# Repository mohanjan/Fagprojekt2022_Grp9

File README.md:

CAPNA
=======================

## What is CAPNA?
CAPNA (Complementary Audio Processor Network Architecture), is a network configuration of individual CAPs (Complementary Audio Processor), each running different DSP applications. This network is synthesized from a con- figuration XML file, which allows the user to specify the interconnections between multible CAPs and the program each CAP runs. The intention with this architecture is to be an uncomplicated, scalable and application tailored digital signal processing.
CAPNA enables the user to accelerate algorithms within digital signal processing (DSP) such as FIR-filtering, machine learning (ML) such as Wavenet and arithmetic calculations such as summation or multiplication. For further explanation of our project please see the [poster](Poster-GRP09-COMPUTE22-1-DSP.pdf) and the [paper](PAPER_GRP09_COMPUTE22-1.pdf)

## Usage
CAPNA is setup using an [XML configuration file](Config) and programmed using [assembly files](Programs).
Once programmed and configured, chisel3 is then used to compile the CAPNA-network into a verilog file which is called DSP.V.

## Recomended development environment
To ease any development on or using CAPNA, [vowstar](https://github.com/vowstar) has made a dockerfile from which an working development debian enviroment can be created and used. we have added verilator to this file and included it here. his original repo can be found here: [https://github.com/vowstar/chisel3-docker](https://github.com/vowstar/chisel3-docker).
The environment contains the following tools:
- [git](https://git-scm.com/)
- [wget](https://www.gnu.org/software/wget/)
- bc(basic calculator)
- [rsync](https://linux.die.net/man/1/rsync)
- [gnupg gnu privacy guard](https://gnupg.org/)
- [curl](https://curl.se/)
- [zip/unzip](http://infozip.sourceforge.net/)
- [make](https://www.gnu.org/software/make/)
- [SBT](https://www.scala-sbt.org/)
- [Chisel3](https://github.com/chipsalliance/chisel3)
- [Verilator](https://www.veripool.org/verilator/)
- [Icaros verilog](http://iverilog.icarus.com/)
- [gtkwave](http://gtkwave.sourceforge.net/)
- [python3](https://www.python.org/)
- Vim
- build essentials(GNU debugger, g++/GNU compiler collection)
- default-jdk-headless
- tools for vivado

### Installation
Note: we recommend to install docker desktop and use the docker image to build a container to insure the function of CAPNA regardless of which system you are using.

To deploy a docker container using the image do the following:
Firstly build the image via the dockerfile calling it chisel3_dev using the command below
```cmd
docker build <path of folder containing dockerfile> -t chisel3_dev
```
To insure the build please check that it is there when the images are listed:

```cmd
docker image ls 
```

Then deploy a container called dev_container and run a bash terminal using the chisel3_dev image and mounting the capna folder location:

```cmd
docker run -it  --name dev_container -v <path\\CAPNA>:/<name of folder in the container> chisel3_dev
```

To manage the container use docker desktop.

To start another terminal using the runnning container dev_container use:
```cmd
docker exec -it dev_container bash
```

To install the tools mentioned above on a linux distribution or WSL(windows subsystem linux) copy paste the following into a bash terminal:
```bash
sudo apt-get update \
&& apt-get install -y \
git \
curl \
unzip \
zip \
verilator \
iverilog \
make \
gtkwave \
&& sudo curl -s "https://get.sdkman.io" | bash \
&& sdk install sbt \
&& sdk install java 11.0.15-tem \
```
### Uninstalling
To uninstall the tools used in the development environment cope paste the following into a bash terminal:
```bash
apt remove \
git \
curl \
unzip \
zip \
verilator \
iverilog \
make \
gtkwave \
rm -rf ~/.sdkman
```

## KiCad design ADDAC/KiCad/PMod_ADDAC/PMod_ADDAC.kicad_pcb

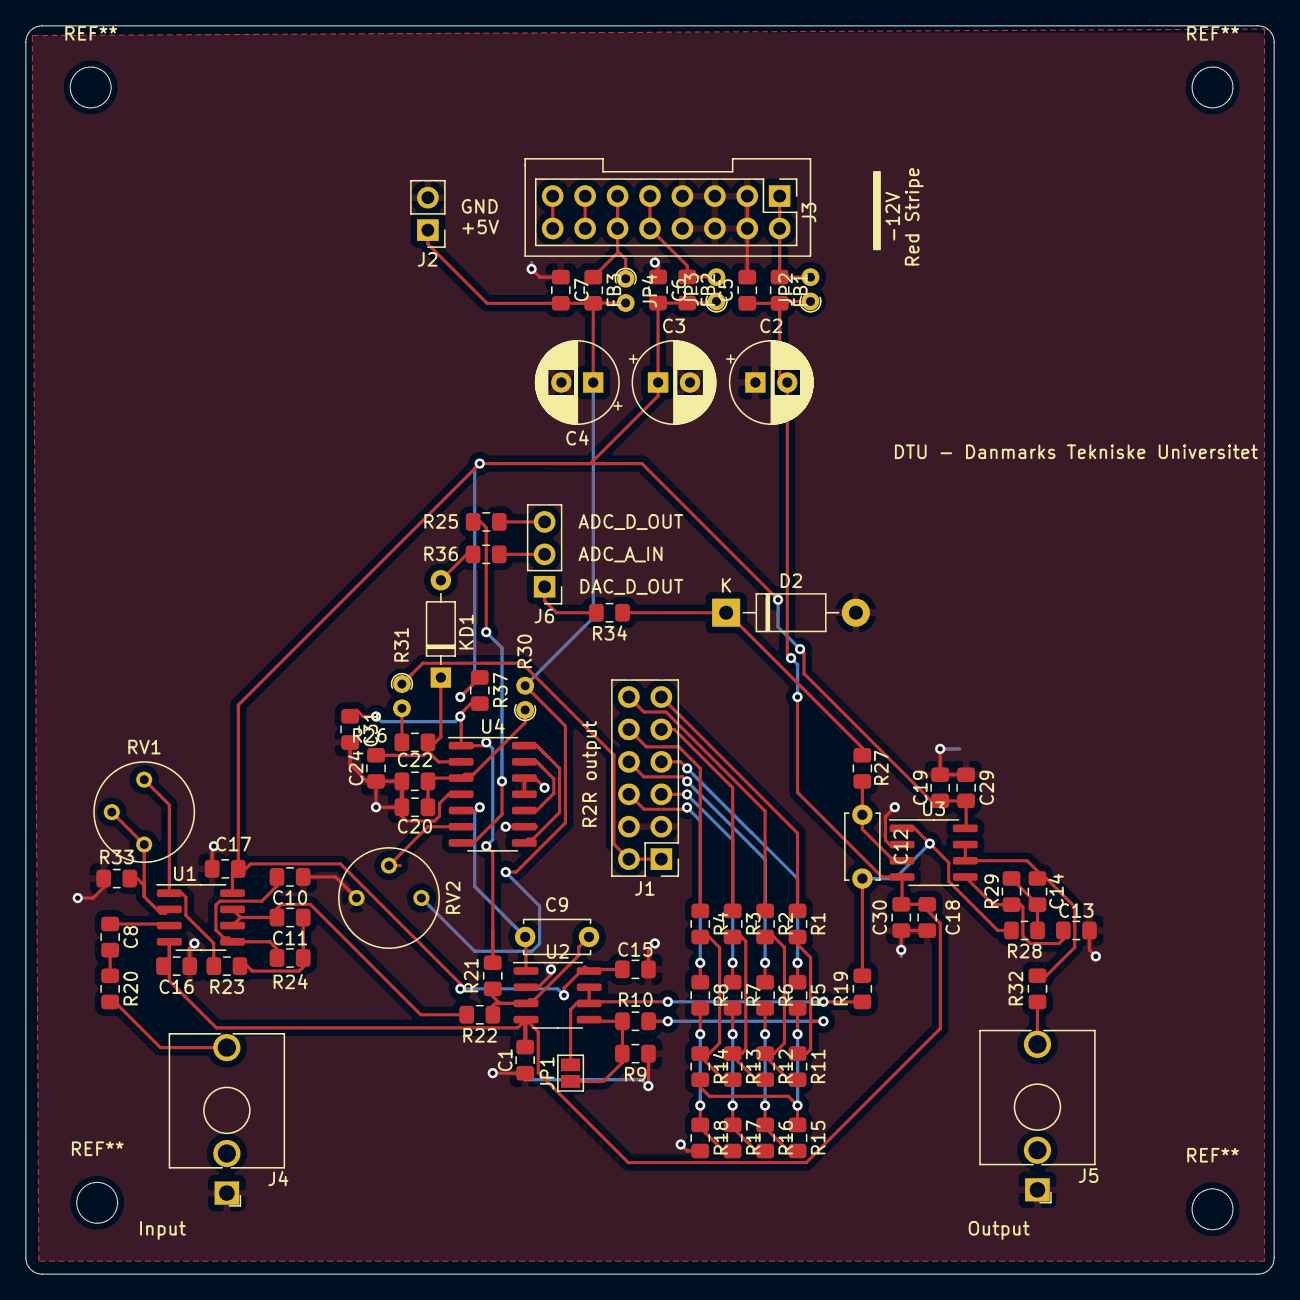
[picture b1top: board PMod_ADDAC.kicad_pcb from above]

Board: 2 copper layers, 97.8 x 97.8 mm, 82 parts (0 on the bottom side), 57 nets.

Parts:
C1, C15: 100; C_0805_2012Metric_Pad1.15x1.40mm_HandSolder
C2, C3, C4: 47u; CP_Radial_D6.3mm_P2.50mm
C5, C6, C7, C10, C11, C13, C14, C16, C17, C18, C19: 10n; C_0805_2012Metric_Pad1.15x1.40mm_HandSolder
C8, C22, C29, C30: 100n; C_0805_2012Metric_Pad1.15x1.40mm_HandSolder
C9, C12: variable; C_Disc_D5.0mm_W2.5mm_P5.00mm
C20: 47n; C_0805_2012Metric_Pad1.15x1.40mm_HandSolder
C24, C31: 15p; C_0805_2012Metric_Pad1.15x1.40mm_HandSolder
D1: BAT43; D_DO-35_SOD27_P7.62mm_Horizontal
D2: 3v9; D_DO-41_SOD81_P10.16mm_Horizontal
FB1, FB2, FB3: Ferrite_Bead_Small; R_0805_2012Metric_Pad1.15x1.40mm_HandSolder
J1: Conn_01x12_Male; PinHeader_2x06_P2.54mm_Vertical
J2: Basys power; PinHeader_1x02_P2.54mm_Vertical
J3: Eurorack Power Connector; PinHeader_2x08_P2.54mm_Vertical
J4, J5: AudioJack2_SwitchT; Jack_3.5mm_QingPu_WQP-PJ398SM_Vertical_CircularHoles
J6: Conn_01x03_Male; PinHeader_1x03_P2.54mm_Vertical
JP1: Jumper_2_Open; SolderJumper-2_P1.3mm_Open_Pad1.0x1.5mm
JP2, JP3, JP4: Jumper_NO_Small; R_Axial_DIN0204_L3.6mm_D1.6mm_P1.90mm_Vertical
R1, R2, R3, R4, R5, R6, R7, R8, R9, R18: 2k; R_0805_2012Metric_Pad1.15x1.40mm_HandSolder
R10, R11, R12, R13, R14, R15, R16, R17, R19, R21, R22, R27, R32, R34: 1k; R_0805_2012Metric_Pad1.15x1.40mm_HandSolder
R20: 100k; R_0805_2012Metric_Pad1.15x1.40mm_HandSolder
R23, R24, R28, R29: 820; R_0805_2012Metric_Pad1.15x1.40mm_HandSolder
R25, R36: 200; R_0805_2012Metric_Pad1.15x1.40mm_HandSolder
R26, R33, R37: 10k; R_0805_2012Metric_Pad1.15x1.40mm_HandSolder
R30, R31: 0; R_Axial_DIN0204_L3.6mm_D1.6mm_P1.90mm_Vertical
RV1, RV2: 10k; Potentiometer_Bourns_3339P_Vertical
U1, U2, U3: TL072; SOIC-8_3.9x4.9mm_P1.27mm
U4: LM339; SOIC-14_3.9x8.7mm_P1.27mm

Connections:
+5V: C4.1, C7.2, FB3.2, J2.1, JP4.2, R30.2, RV2.3
+12V: C3.1, C6.2, C15.2, C17.2, C19.2, C29.2, FB2.2, JP3.1, R37.1, U1.8, U2.8, U3.8
-12V: C1.1, C2.2, C5.1, C16.2, C18.2, C30.2, FB1.2, JP2.1, U1.4, U2.4, U3.4
ADC_A_in: J6.2, R36.1
ADC_D_out: J6.3, R25.1
ADC_signal_in: C11.2, R22.2, U1.6, U1.7
DAC_D_out: J6.1, R34.2
DAC_R2R_out: C12.1, R19.2, R28.2, U3.1
GND: C1.2, C2.1, C3.2, C4.2, C5.2, C6.1, C7.1, C10.1, C13.1, C15.1, C16.1, C17.1, C18.1, C19.1, C20.1, C22.1, C24.2, C29.1, C30.1, C31.2, D2.2, J1.3, J1.4, J2.2, J3.3, J3.4, J3.5, J3.6, J3.7, J3.8, J4.S, J5.S, R9.1, R18.2, R33.1, RV2.1, U2.2, U3.2, U4.4, U4.9, U4.11, U4.12
unnamed: C8.1, U1.3
unnamed: C8.2, R20.1
unnamed: C9.1, U2.1, U4.5
unnamed: C9.2, R21.1, R22.1, U2.3
unnamed: C10.2, R24.1, U1.5
unnamed: C11.1, R23.1, R24.2
unnamed: C12.2, R27.1, U3.3
unnamed: C13.2, R29.1, U3.5
unnamed: C14.1, R28.1, R29.2
unnamed: C14.2, R32.2, U3.6, U3.7
unnamed: C20.2, C22.2, R30.1, U4.3
unnamed: C24.1, D1.1, R26.2, U4.2
unnamed: C31.1, R21.2, R37.2, U4.1
unnamed: D1.2, R36.2
unnamed: D2.1, R27.2, R34.1
unnamed: FB1.1, J3.1, J3.2, JP2.2
unnamed: FB2.1, J3.9, J3.10, JP3.2
unnamed: FB3.1, J3.11, J3.12, JP4.1
unnamed: J1.5, R7.1
unnamed: J1.6, R8.1
unnamed: J1.7, R5.1
unnamed: J1.8, R6.1
unnamed: J1.9, R3.1
unnamed: J1.10, R4.1
unnamed: J1.11, R1.1
unnamed: J1.12, R2.1
unnamed: J3.13, J3.14
unnamed: J3.15, J3.16
unnamed: J4.T, R20.2
unnamed: J5.T, R32.1
unnamed: JP1.1, R9.2, R10.1, U2.5
unnamed: JP1.2, R19.1, U2.6, U2.7
unnamed: R1.2, R10.2, R11.1
unnamed: R2.2, R11.2, R12.1
unnamed: R3.2, R12.2, R13.1
unnamed: R4.2, R13.2, R14.1
unnamed: R5.2, R14.2, R15.1
unnamed: R6.2, R15.2, R16.1
unnamed: R7.2, R16.2, R17.1
unnamed: R8.2, R17.2, R18.1
unnamed: R23.2, RV1.3, U1.1
unnamed: R25.2, U4.7
unnamed: R26.1, R31.2
unnamed: R33.2, RV1.1, RV1.2, U1.2
unnamed: RV2.2, U4.6
unnamed: U4.10, U4.13
unnamed: U4.8, U4.14
VCC: J1.1, J1.2, R31.1

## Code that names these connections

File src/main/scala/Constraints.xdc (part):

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
##Pmod Header JA
##Sch name = JA1
#set_property PACKAGE_PIN J1 [get_ports {io_ADIn}]				#ADC_A_in	
	#set_property IOSTANDARD LVCMOS33 [get_ports *]
##Sch name = JA2
#set_property PACKAGE_PIN L2 [get_ports {io_ADOut}]				#ADC_D_out	
#	set_property IOSTANDARD LVCMOS33 [get_ports {JA[1]}]
##Sch name = JA3
#set_property PACKAGE_PIN J2 [get_ports {io_DAOut}]				#DAC_D_out		
#	set_property IOSTANDARD LVCMOS33 [get_ports {JA[2]}]
##Sch name = JA4
#set_property PACKAGE_PIN G2 [get_ports {JA[3]}]					
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
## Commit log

2022-02-07 Kicad_filer
2022-02-10 Create GoodPractices.txt
    This file contains all good practices to be used during the project
2022-02-14 Added DSP module
2022-02-16 ny branch
2022-02-19 Wrote instruction set, Built small 16-bit processor
2022-02-21 software folder added + bit-ifyer
2022-02-21 updated software stuff
2022-02-21 update java file
2022-02-21 Changed instructions
2022-02-24 work on xadc
2022-02-28 Increased memory address bit-width to support 36 kb
2022-03-03 pmodR2R design1
2022-03-06 made singal gen on seeduino
2022-03-07 R2R updated
2022-03-08 R2RDAC update
2022-03-08 fixed R2R orientation
2022-03-09 put adc into chisel. has syntax errrs
2022-03-10 emitted a verilog file
2022-03-14 minor change addac
2022-03-15 Pipelined processor, WIP
2022-03-20 Works
2022-03-21 Added Fir communication
2022-03-21 øøøøøøø
2022-03-21 Cleaned up folders for vivado projects
2022-03-21 changed file name
2022-03-23 Added assembler
2022-03-25 Everything works
2022-03-28 Addi now works with SInt
2022-03-28 removed junk
2022-03-28 lil Cleanup
2022-03-28 mer kicad
2022-03-31 kicad update
2022-03-31 updated PCB
2022-04-03 PCB-progress
2022-04-03 Added pre-assembler
2022-04-04 small bug fix
2022-04-04 Schematic
2022-04-07 Cleaning
2022-04-07 Changed gitignore and XADC files
2022-04-13 pcb done?
2022-04-14 Updated ISA
2022-04-17 changed IS, updated assembler, added SPI RAM controller
2022-04-18 Added Quad SPI write
2022-04-20 Cleanup
2022-04-20 comit
2022-04-21 added bundle classes
2022-04-21 Changed MemPort
2022-04-22 Small changes
2022-04-23 Added new top module
2022-04-23 Added data memory arbiter
2022-04-25 Updated git ignore
2022-05-02 Generated IBOM
2022-05-05 diller
2022-05-05 created io file
2022-05-05 seperated input and output controller
2022-05-05 added a master for the IOcontroller
2022-05-05 added count register
2022-05-05 small progress
2022-05-05 moved all IO related files into seperate folder
2022-05-06 test
2022-05-07 IO FIlter and design description
2022-05-08 Started to connect up DSP and IO
2022-05-18 Added verilator tester
2022-05-27 changed instructionmemory
2022-05-28 fixed ALU bug
2022-05-30 IO Filter (non tested)
2022-05-30 IO lowpass filter coeffs
2022-05-30 updated todo
2022-05-30 updated IOFilter
2022-05-31 WIP IOFILTER with failing test due to weird $anonfun$new$3 error
2022-06-01 Fixed memory bug
2022-06-02 WIP IOFILTER with signed bitshift and masking error
2022-06-02 small change
2022-06-04 fixed jmp bug
2022-06-06 Fixed memory write bug
2022-06-06 qdawd
2022-06-07 I/O Controller ~maybe~ works Dont know how to test at this moment
2022-06-08 IOFilter: data out ikke testet og mangler at fikse io.completed timing
2022-06-08 IOFilter: data out ikke testet men io.completed er fixed
2022-06-08 IOFilter: convolution af samples er inskrevet
2022-06-08 Multicore processor ready
2022-06-08 Arduino tests
2022-06-08 figure
2022-06-08 Assemlber in XML
2022-06-09 Multicore processor finished
2022-06-10 Added IOFilter compatibility
2022-06-10 Working symmetric IOFilter <3
2022-06-10 Fixed assembler xor bug
2022-06-10 IOF halway implemented
2022-06-10 yeesh
2022-06-10 Added data-memory size and SPI-ram offset to config xml
2022-06-10 forgot to svae changes
2022-06-10 Reformatted IOFilter and changed the internal cyclic input and output buffer and their pointers to update using ADCWaveIN and DACWaveIn respectively when ADCEnable and DACEnable respectively is high.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
2022-06-13 Fixed assember bug
2022-06-13 Added test config to xml
2022-06-13 added comments to core.scala
2022-06-13 IOFilter enable convention change! If ADCenable and DACenable are off then convolution starts
2022-06-13 comments added to ALU.scala
2022-06-13 Added mac and fixed point mult, and changed spi on top module
2022-06-13 Added tristate driver
2022-06-13 sampletype signal wont toggle
2022-06-13 Comments
2022-06-14 arduino test code
2022-06-14 IO_test created
2022-06-15 Added instructions and fixed mem bug
2022-06-15 FIREngine(VIRKER IKKE)
2022-06-15 Stage before merge
2022-06-15 Fixed arithmetic shift
2022-06-15 Added input/output filter to xml, fixed bug in swi and lwi instructions
2022-06-15 Update and rename TestIOConstraints.xdc.txt to Constraints.xdc
    fix xdc
2022-06-15 Added binary to li
2022-06-16 New branch
2022-06-16 IOFILTER VIRKER
2022-06-16 FIRFIlter VIRKER IKKE
2022-06-16 Added text to sbt run
2022-06-16 Fixing timing in incontroller
2022-06-16 cant figure out why no output
2022-06-16 IOtestupdate
2022-06-16 Commit for johannes
2022-06-16 Remade IOMaster
2022-06-16 Added Config file folder, and command prompt
2022-06-16 Fixed error
2022-06-16 Sine wave generation
2022-06-16 PDM test fix
2022-06-17 Added config file print
2022-06-17 commented out xml feature so we can generate verilog
2022-06-17 ConvEnable tilføjet til IOFilter
2022-06-17 updated test
2022-06-17 maybe IO works a little bit?
2022-06-17 Changed names of fir connections
2022-06-17 this sounds really bad
2022-06-17 rettelser
2022-06-17 fixed IOFilter ift. selvtest men ikke ift memory
2022-06-17 fixed IOFilter virker helt
2022-06-17 added count var to toggle enables in iomaster
2022-06-17 Fixed datamem
2022-06-17 some bad sounds are present?
2022-06-17 Fixed assembler bug
2022-06-17 hardly working IOtest
2022-06-17 Too many clock cycles to test vitually
2022-06-17 doesn't work properly...
2022-06-17 changed stuff
2022-06-17 johan leger med filtre
2022-06-18 brrr
2022-06-18 SOUND!!!
2022-06-18 added Sint support
2022-06-18 uint
2022-06-18 eurorack
2022-06-19 in controller with Uint
2022-06-19 Fixed assembler
2022-06-19 optimization?
2022-06-19 proper SINT
2022-06-19 maybe?
2022-06-19 Build I2S Adc module
2022-06-19 Added sample folder
2022-06-20 Parametriziable input controller
2022-06-20 Added make, bitches
2022-06-21 Update build.sbt
    nice CAPNA
2022-06-21 Added make test, Fixed multicore config file
2022-06-21 WORKING!!!!!!
2022-06-22 Did stuff
2022-06-23 New FIR-Engine changes
2022-06-23 Create FIREngineTest
2022-06-23 Removed file
2022-06-23 Added io switches
2022-07-05 Added paper
2022-07-05 Uploaded paper
2022-08-11 create Dockerfile
2022-08-11 Update Readme with regards to Dockerfile
2022-08-12 Update Dockerfile
2022-09-04 Arduino test files moved, renamed branch
2022-09-05 jotting down ideas
